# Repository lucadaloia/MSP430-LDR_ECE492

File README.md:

# MSP430-LDR_ECE492 
### ECE 492 (Embedded Systems Hardware Design) Project

## 📝 Overview
This project involved the design and manufacturing of a microcontroller-based system focused on analog signal acquisition and real-time user interaction. The system utilizes a photoresistor (LDR) for environmental sensing and a tactile user interface, all managed by a custom-designed PCB and optimized C firmware.

The core of the system is the **MSP430FR2355**, utilizing its 10-bit ADC12 module and hardware timers to create a responsive, low-power monitoring tool.

## 🛠 Hardware Specifications
- **MCU:** MSP430
- **Sensors:** Photoresistor (Analog A1) & Thumbwheel Potentiometer (Analog A2)
- **User Input:** 3x Tactile Pushbuttons (Hardware Interrupts)
- **Visual Output:** 4x LED Status Indicators (Blue, Yellow, Green, Red)

## 📂 Project Structure
- `main.c`: Central application logic and LED threshold management.
- `ADC.c`: 10-bit ADC12 configuration and sampling logic.
- `interrupts.c`: ISRs for Port 2 (Mode switching), Timer B (10Hz trigger), and ADC.
- `ports.c`: GPIO and Peripheral multiplexing setup.
- `timers.c`: Timer_B0 configuration using ACLK (~32.768 kHz).
- `globals.c`: Volatile variable definitions for shared system state.

## ⚙️ Technical Highlights
### 1. Automated ADC Chaining
To minimize CPU overhead, the firmware uses a "chaining" logic within the ADC Interrupt Service Routine. Once the photoresistor is sampled, the ISR automatically reconfigures the multiplexer to sample the thumbwheel, ensuring all sensor data is current without blocking the main loop.

### 2. Interrupt-Driven State Machine
The system switches between three operating modes via Port 2 interrupts:
- **Mode 1:** All-or-nothing binary threshold.
- **Mode 2:** Graduated response (LEDs light up sequentially based on intensity).
- **Mode 3:** Environmental calibration and baseline setting.

---
**Author:** Luca Daloia  
**Project Date:** Spring 2026  
**Course:** ECE 492

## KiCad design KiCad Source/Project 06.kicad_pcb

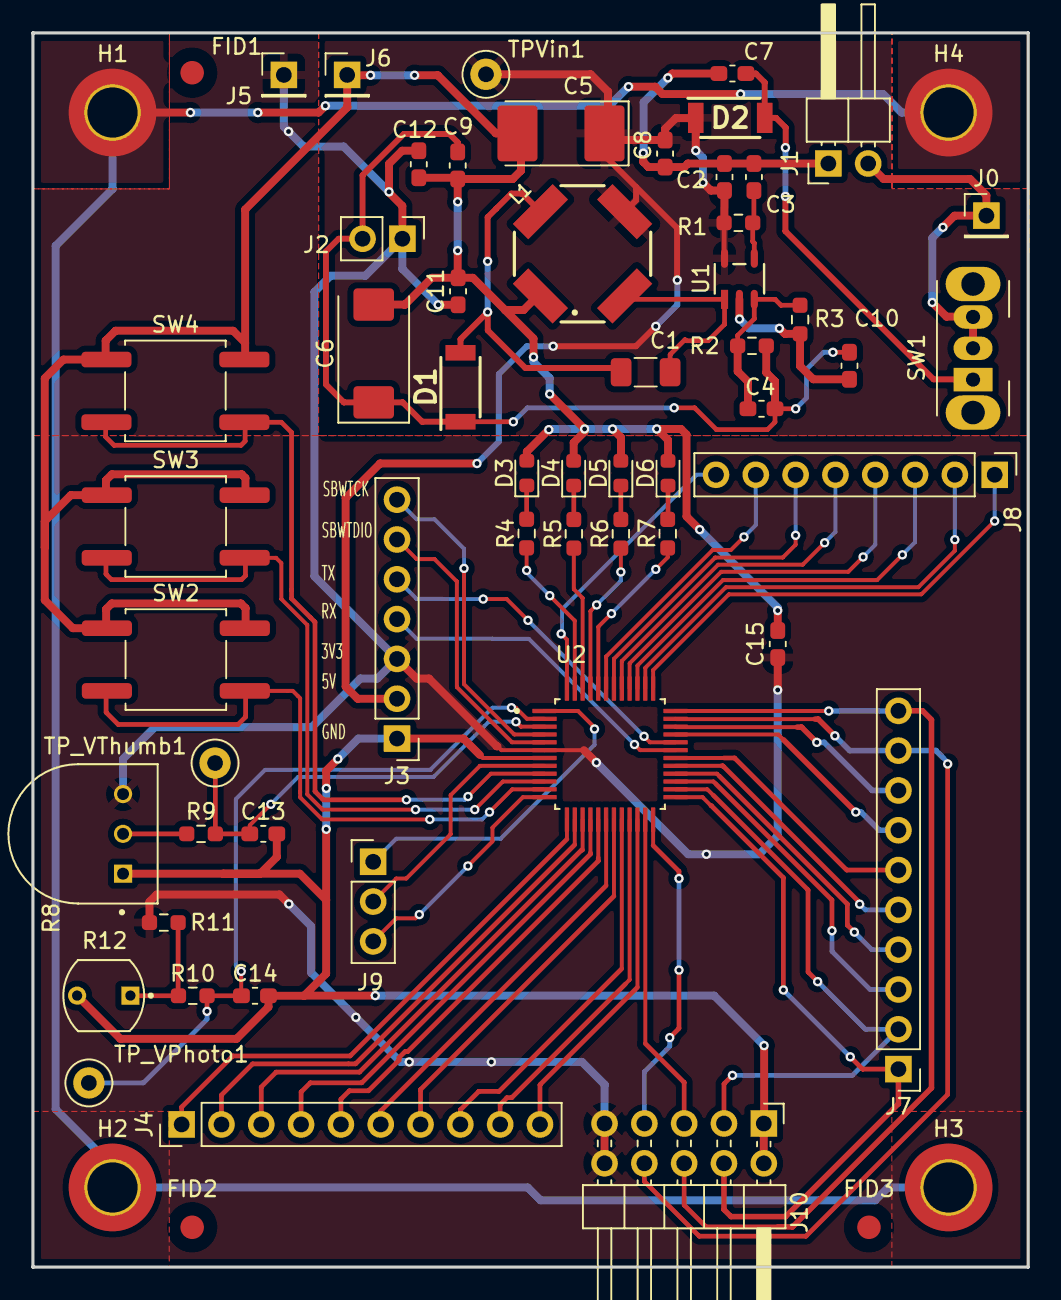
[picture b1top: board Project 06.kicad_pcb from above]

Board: 2 copper layers, 63.5 x 78.7 mm, 61 parts (0 on the bottom side), 63 nets.

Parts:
C1: 1.0UF; C_1206_3216Metric_Pad1.33x1.80mm_HandSolder
C2, C7, C8, C9, C10, C11, C12: 10UF; C_0603_1608Metric_Pad1.08x0.95mm_HandSolder
C3, C4: 470PF; C_0603_1608Metric_Pad1.08x0.95mm_HandSolder
C5: 22UF; CP_EIA-7132-20_AVX-U
C6: 100UF; CP_EIA-7343-40_Kemet-Y
C13, C14: 0.1uF; C_0603_1608Metric_Pad1.08x0.95mm_HandSolder
C15: 0.1UF; C_0603_1608Metric_Pad1.08x0.95mm_HandSolder
D1, D2: PMEG3020BEP,115
D3: LTST-C190GKT; LED_0603_1608Metric
D4: LTST-C190KRKT; LED_0603_1608Metric
D5: LTST-C190KSKT; LED_0603_1608Metric
D6: LTST-C190TBKT; LED_0603_1608Metric
FID1, FID2, FID3: Fiducial; Fiducial_1.5mm_Mask3mm
H1, H2, H3, H4: MountingHole_Pad; MountingHole_3.2mm_M3_DIN965_Pad_TopOnly
J0, J5, J6: Conn_01x01; PinHeader_1x01_P2.54mm_Vertical
J1: Conn_01x02; PinHeader_1x02_P2.54mm_Horizontal
J2: Conn_01x02; PinHeader_1x02_P2.54mm_Vertical
J3: Conn_01x07_Pin; PinHeader_1x07_P2.54mm_Vertical
J4, J7: Conn_01x10_Pin; PinHeader_1x10_P2.54mm_Vertical
J8: Conn_01x08_Pin; PinHeader_1x08_P2.54mm_Vertical
J9: Conn_01x05_Pin; PinHeader_1x03_P2.54mm_Vertical
J10: Conn_02x05_Odd_Even; PinHeader_2x05_P2.54mm_Horizontal
L1: WE-TDC_8038
R1: 10.0K; R_0603_1608Metric_Pad0.98x0.95mm_HandSolder
R2: 12K; R_0603_1608Metric_Pad0.98x0.95mm_HandSolder
R3: 20K; R_0603_1608Metric_Pad0.98x0.95mm_HandSolder
R4, R5, R6, R7: 220; R_0603_1608Metric_Pad0.98x0.95mm_HandSolder
R8: 3352T-1-103LF; TRIM_3352T-1-103LF
R9, R10: 1k; R_0603_1608Metric_Pad0.98x0.95mm_HandSolder
R11: 10k; R_0603_1608Metric_Pad0.98x0.95mm_HandSolder
R12: PDV-P8103; PHODET_PDV-P8103
SW1: SW_SPDT; SW_Slide_SPDT_Angled_CK_OS102011MA1Q
SW2, SW3, SW4: SW_DIP_x01; SW_Push_1P1T_NO_CK_KSC9xxG
TPVin1: TestPoint; TestPoint_Loop_D1.80mm_Drill1.0mm_Beaded
TP_VPhoto1: TestPoint; TestPoint_Loop_D1.80mm_Drill1.0mm_Beaded
TP_VThumb1: TestPoint; TestPoint_Loop_D1.80mm_Drill1.0mm_Beaded
U1: LT1935ES5-TRPBF
U2: MSP430FR2355TPT

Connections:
/Power Circuit/*SHDN: C3.1, R1.2, U1.4 (*SHDN)
/Power Circuit/FB: C4.2, R2.2, R3.1, U1.3 (FB)
/Power Circuit/Raw_Bat: J0.1, J1.2, SW1.2 (B), SW1.3 (C)
/Processor Schematic/LED1: R4.1, U2.47 (P3.0/MCLK)
/Processor Schematic/LED2: R5.1, U2.46 (P3.1/OA2O)
/Processor Schematic/LED3: R6.1, U2.45 (P3.2/OA2-)
/Processor Schematic/LED4: R7.1, U2.44 (P3.3/OA2+)
/Processor Schematic/P1.2: J9.1, U2.1 (P1.2/UCB0SIMO/UCB0SDA/TB0TRG/OA0-/A2/VE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)
/Processor Schematic/P1.3: J8.8, U2.48 (P1.3/UCB0SOMI/UCB0SCL/OA0+/A3)
/Processor Schematic/P1.4: J7.8, U2.34 (P1.4/UCA0STE/TCK/A4)
/Processor Schematic/P1.5: J7.7, U2.33 (P1.5/UCA0CLK/TMS/OA1O/A5)
/Processor Schematic/P2.0: J7.6, U2.30 (P2.0/TB1.1/COMP0.O)
/Processor Schematic/P2.1: J7.5, U2.29 (P2.1/TB1.2/COMP1.O)
/Processor Schematic/P2.2: J7.4, U2.28 (P2.2/TB1CLK)
/Processor Schematic/P2.3: J7.3, U2.27 (P2.3/TB1TRG)
/Processor Schematic/P2.4: SW2.1, U2.11 (P2.4/COMP1.1)
/Processor Schematic/P2.5: SW3.1, U2.10 (P2.5/COMP1.0)
/Processor Schematic/P2.6: SW4.1, U2.9 (P2.6/MCLK/XOUT)
/Processor Schematic/P2.7: J9.2, U2.8 (P2.7/TB0CLK/XIN)
/Processor Schematic/P3.4: J8.2, U2.38 (P3.4/SMCLK)
/Processor Schematic/P3.5: J8.1, U2.37 (P3.5/OA3O)
/Processor Schematic/P4.4: J4.3, U2.15 (P4.4/UCB1STE)
/Processor Schematic/P4.5: J4.2, U2.14 (P4.5/UCB1CLK)
/Processor Schematic/P4.6: J4.1, U2.13 (P4.6/UCB1SIMO/UCB1SDA)
/Processor Schematic/P4.7: J9.3, U2.12 (P4.7/UCB1SOMI/UCB1SCL)
/Processor Schematic/P5.0: J8.7, U2.43 (P5.0/TB2.1/MFM.RX/A8)
/Processor Schematic/P5.1: J8.6, U2.42 (P5.1/TB2.2/MFM.TX/A9)
/Processor Schematic/P5.2: J8.5, U2.41 (P5.2/TB2CLK/A10)
/Processor Schematic/P5.3: J8.4, U2.40 (P5.3/TB2TRG/A11)
/Processor Schematic/P5.4: J8.3, U2.39 (P5.4)
/Processor Schematic/P6.0: J4.10, U2.22 (P6.0/TB3.1)
/Processor Schematic/P6.1: J4.9, U2.21 (P6.1/TB3.2)
/Processor Schematic/P6.2: J4.8, U2.20 (P6.2/TB3.3)
/Processor Schematic/P6.3: J4.7, U2.19 (P6.3/TB3.4)
/Processor Schematic/P6.4: J4.6, U2.18 (P6.4/TB3.5)
/Processor Schematic/P6.5: J4.5, U2.17 (P6.5/TB3.6)
/Processor Schematic/P6.6: J4.4, U2.16 (P6.6/TB3CLK)
/Processor Schematic/SBWTCK: J3.7, U2.4 (TEST/SBWTCK)
/Processor Schematic/SBWTDIO: J3.6, U2.5 (~RST/NMI/SBWTDIO)
/Processor Schematic/UART_RX: J3.4, U2.31 (P1.7/UCA0TXD/UCA0SIMO/TB0.2/TDO/OA1+/A7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)
/Processor Schematic/UART_TX: J3.5, U2.32 (P1.6/UCA0RXD/UCA0SOMI/TB0.1/TDI/TCLK/OA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)
/Sensor Schematic/Thumb_OUT: R8.2, R9.1
CPU_RXDA: J10.7 (Pin_3), U2.24 (P4.2/UCA1RXD/UCA1SOMI/~UCA1RXD)
CPU_TXDA: J10.5, U2.23 (P4.3/UCA1TXD/UCA1SIMO/~UCA1TXD)
GND: C2.2, C3.2, C5.2, C6.2, C7.2, C8.2, C9.2, C10.2, C11.2, C12.2, C13.2, C14.2, C15.2, D3.2 (C), D4.2 (C), D5.2 (C), D6.2 (C), J1.1, J3.1, J6.1, J10.1 (Pin_9), J10.2 (Pin_10), L1.1, R3.2, R8.1, R12.2, SW2.2, SW3.2, SW4.2, U1.2 (GND), U2.7 (DVSS)
GNDPWR: H1.1, H2.1, H3.1, H4.1
IOT_BOOTA: J7.1, J10.4 (Pin_8), U2.25 (P4.1/UCA1CLK)
IOT_EN: J7.2, J10.3 (Pin_7), U2.26 (P4.0/UCA1STE/ISOTXD/ISORXD)
IOT_LINK: J7.10, J10.6, U2.36 (P3.6/OA3-)
IOT_RUN: J7.9, J10.8 (Pin_4), U2.35 (P3.7/OA3+)
unnamed: C1.1, D1.2 (A), L1.4
unnamed: C4.1, C6.1, C9.1, C10.1, D1.1 (K), J2.2, R2.1
unnamed: C7.1, D2.2 (A), SW1.1 (A)
unnamed: D3.1 (A), R4.2
unnamed: D4.1 (A), R5.2
unnamed: D5.1 (A), R6.2
unnamed: D6.1 (A), R7.2
unnamed: R10.1, R11.1, R12.1
unnamed: C1.2, L1.2, U1.1 (SW)
PWR3_3: C11.1, C12.1, C15.1, J2.1, J3.3, J5.1, J10.9 (Pin_1), J10.10 (Pin_2), R8.3, R11.2, U2.6 (DVCC)
PWR5D+: C2.1, C5.1, C8.1, D2.1 (K), J3.2, L1.3, R1.1, TPVin1.1, U1.5 (VIN)
V_PHOTO: C14.1, R10.2, TP_VPhoto1.1, U2.2 (P1.1/UCB0CLK/ACLK/OA0O/COMP0.1/A1)
V_THUMB: C13.1, R9.2, TP_VThumb1.1, U2.3 (P1.0/UCB0STE/SMCLK/COMP0.0/A0/VEREF+)

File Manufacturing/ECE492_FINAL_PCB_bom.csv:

Designator,Footprint,Quantity,Value,LCSC Part #
C1,1206,1,1.0UF,
"C10, C11, C12, C16, C17, C18, C19, C2, C20, C21, C22, C23, C24, C25, C7, C8, C9",0603,17,10UF,
"C13, C14, C15",0603,3,0.1uF,
"C3, C4",0603,2,470PF,
C5,CP_EIA-7132-20_AVX-U,1,22UF,
C6,CP_EIA-7343-40_Kemet-Y,1,100UF,
"D1, D2","PMEG3020BEP,115",2,"PMEG3020BEP,115",
D3,0603,1,LTST-C190GKT,
D4,0603,1,LTST-C190KRKT,
D5,0603,1,LTST-C190KSKT,
D6,0603,1,LTST-C190TBKT,
"J0, J5, J6",PinHeader_1x01_P2.54mm_Vertical,3,Conn_01x01,
J1,PinHeader_1x02_P2.54mm_Horizontal,1,Conn_01x02,
J10,PinHeader_2x05_P2.54mm_Horizontal,1,Conn_02x05_Odd_Even,
J2,PinHeader_1x02_P2.54mm_Vertical,1,Conn_01x02,
J3,PinHeader_1x07_P2.54mm_Vertical,1,Conn_01x07_Pin,
"J4, J7",PinHeader_1x10_P2.54mm_Vertical,2,Conn_01x10_Pin,
J8,PinHeader_1x08_P2.54mm_Vertical,1,Conn_01x08_Pin,
J9,PinHeader_1x03_P2.54mm_Vertical,1,Conn_01x05_Pin,
L1,WE-TDC_8038,1,WE-TDC_8038,
R1,0603,1,10.0K,
"R10, R9",0603,2,1k,
R11,0603,1,10k,
R12,PHODET_PDV-P8103,1,PDV-P8103,
R2,0603,1,12K,
R3,0603,1,20K,
"R4, R5, R6, R7",0603,4,220,
R8,TRIM_3352T-1-103LF,1,3352T-1-103LF,
SW1,SW_Slide_SPDT_Angled_CK_OS102011MA1Q,1,SW_SPDT,
"SW2, SW3, SW4",SW_Push_1P1T_NO_CK_KSC9xxG,3,SW_DIP_x01,
"TPVIN1, TP_VPHOTO1, TP_VTHUMB1",TestPoint_Loop_D1.80mm_Drill1.0mm_Beaded,3,TestPoint,
U1,LT1935ES5-TRPBF,1,LT1935ES5-TRPBF,
U2,MSP430FR2355TPT,1,MSP430FR2355TPT,

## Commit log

2026-05-09 Enhance README with detailed project information
    Expanded the README to include project overview, hardware specifications, project structure, technical highlights, and usage instructions.
2026-05-09 Remove usage instructions from README
    Removed usage instructions from the README.
2026-05-09 Added MSP430 C Frirmware Folder
2026-05-09 Revise author, date, and course details in README
    Updated author name, project date, and course information in README.
